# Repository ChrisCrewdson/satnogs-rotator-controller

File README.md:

# SatNOGS Rotator Controller

Firmware and electronics designs for [SatNOGS Rotator](https://github.com/satnogs/satnogs-rotator/).

Repository includes all source files for PCB's and firmware for the SatNOGS rotator controller assembly.

## Documentation

More information can be found in our [documentation](http://satnogs.org/documentation/hardware/), or our [wiki](https://wiki.satnogs.org).

Please check the documentation to find which release of the rotator controller matches your mechanical rotator version.

## Repository policy
SatNOGS hardware repositories only track source design files. All needed derivative files (e.g. stl, grb etc) for production are created per release, packaged in an archive and uploaded linked to a  [release](https://github.com/satnogs/satnogs-rotator-controller/releases).

Each major release (x.0.0) is branched out of master. Subsequent fixes (minor or not) are commited on those branches and tagged accordingly.

Master branch is most times under active development, so expect things to break. For production ready and previous releases source files check tags and branches.

## License

&copy; 2014-2015 [Libre Space Foundation](http://librespacefoundation.org).

Licensed under the [CERN OHLv1.2](LICENSE).

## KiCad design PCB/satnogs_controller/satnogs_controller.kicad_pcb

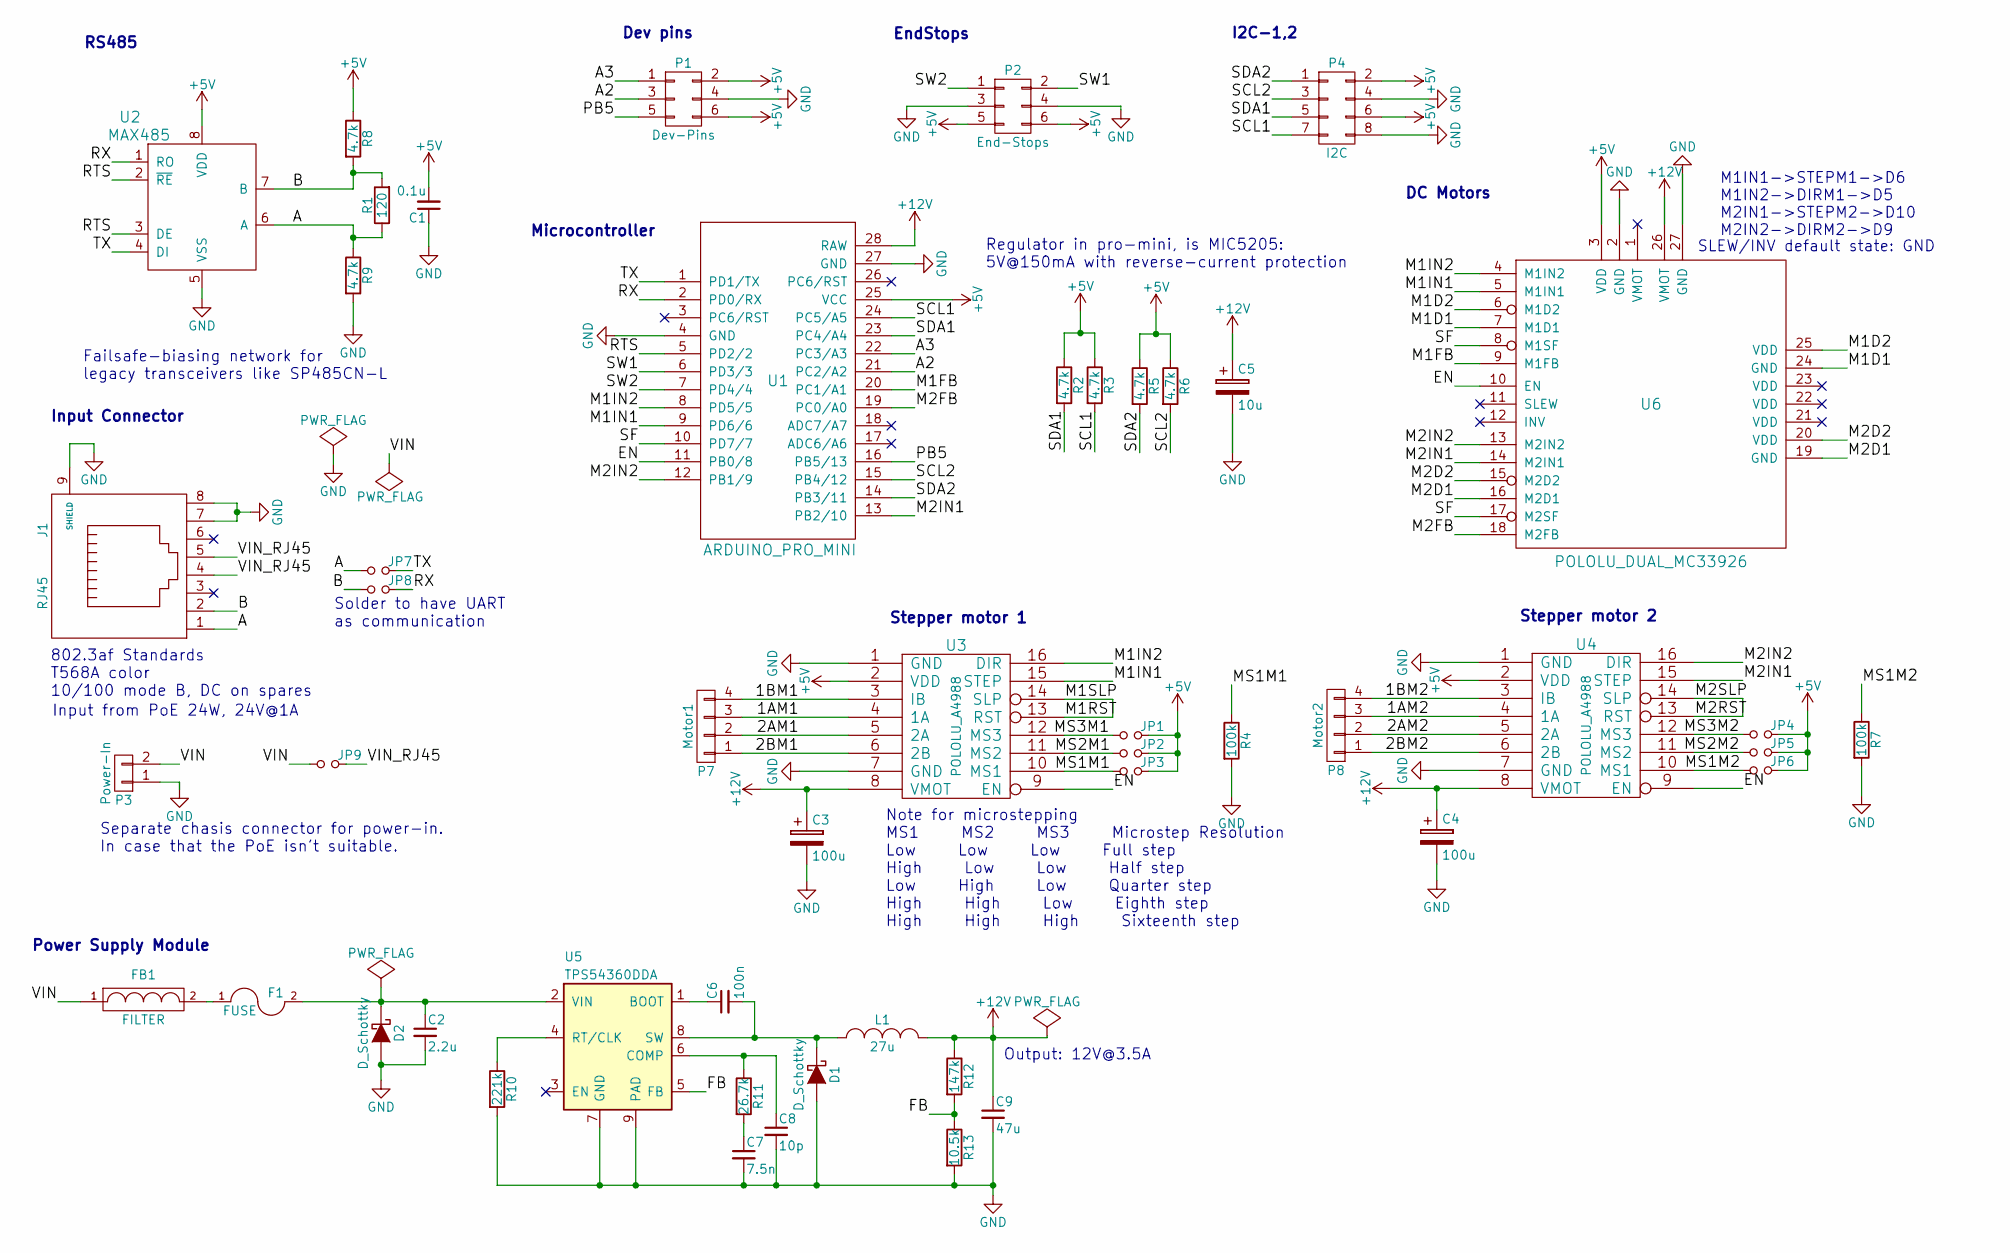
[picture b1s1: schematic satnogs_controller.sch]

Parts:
C1: 0.1u; C_0805_HandSoldering
C2: 2.2u; C_1210
C3, C4: 100u; C_Radial_D6.3_L11.2_P2.5
C5: 10u; C_Radial_D6.3_L11.2_P2.5
C6: 100n; C_0805_HandSoldering
C7: 7.5n; C_0805_HandSoldering
C8: 10p; C_0805_HandSoldering
C9: 47u; C_1210
D1, D2: D_Schottky; DO-214AB
F1: FUSE; Fuse_SMD
FB1: FILTER; R_0805_HandSoldering
J1: RJ45; RJ45_8
JP1, JP2, JP3, JP4, JP5, JP6, JP7, JP8, JP9: Jumper_NO_Small; R_0805_HandSoldering
L1: 27u; bourns-srr1210
P1: Dev-Pins; Pin_Header_Straight_2x03
P2: End-Stops; Pin_Header_Straight_2x03
P3: Power-In; WireConnection_2.00mmDrill
P4: I2C; Pin_Header_Straight_2x04
P7: Motor1; bornier4
P8: Motor2; bornier4
R1: 120; R_0805_HandSoldering
R2, R3, R5, R6, R8, R9: 4.7k; R_0805_HandSoldering
R4, R7: 100k; R_0805_HandSoldering
R10: 221k; R_0805_HandSoldering
R11: 26.7k; R_0805_HandSoldering
R12: 147k; R_0805_HandSoldering
R13: 10.5k; R_0805_HandSoldering
U1: ARDUINO_PRO_MINI; arduino-pro-mini
U2: MAX485; SOIC-8_3.9x4.9mm_Pitch1.27mm
U3, U4: POLOLU_A4988; pololu-a4988
U5: TPS54360DDA; HSOP-8
U6: POLOLU_DUAL_MC33926; pololu-dual-mc33926

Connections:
+5V: C1.2, JP1.2, JP2.2, JP3.2, JP4.2, JP5.2, JP6.2, P1.2, P1.6, P2.5, P2.6, P4.2, P4.6, R2.1, R3.1, R5.1, R6.1, R8.1, U1.25 (VCC), U2.8 (VDD), U3.2 (VDD), U4.2 (VDD), U6.3 (VDD)
+12V: C3.1, C4.1, C5.1, C9.1, L1.2, R12.1, U1.28 (RAW), U3.8 (VMOT), U4.8 (VMOT), U6.26 (VMOT)
/1AM1: P7.3, U3.4 (1A)
/1AM2: P8.3, U4.4 (1A)
/1BM1: P7.4, U3.3 (IB)
/1BM2: P8.4, U4.3 (IB)
/2AM1: P7.2, U3.5 (2A)
/2AM2: P8.2, U4.5 (2A)
/2BM1: P7.1, U3.6 (2B)
/2BM2: P8.1, U4.6 (2B)
/A: J1.1, JP7.1, R1.1, R9.1, U2.6 (A)
/A2: P1.3, U1.21 (PC2/A2)
/A3: P1.1, U1.22 (PC3/A3)
/B: J1.2, JP8.1, R1.2, R8.2, U2.7 (B)
/EN: U1.11 (PB0/8), U3.9 (EN), U4.9 (EN), U6.10 (EN)
/FB: R12.2, R13.1, U5.5 (FB)
/M1D1: U6.7 (M1D1), U6.24 (GND)
/M1D2: U6.6 (M1D2), U6.25 (VDD)
/M1FB: U1.20 (PC1/A1), U6.9 (M1FB)
/M1IN1: U1.9 (PD6/6), U3.15 (STEP), U6.5 (M1IN1)
/M1IN2: U1.8 (PD5/5), U3.16 (DIR), U6.4 (M1IN2)
/M1RST: U3.13 (RST), U3.14 (SLP)
/M2D1: U6.16 (M2D1), U6.19 (GND)
/M2D2: U6.15 (M2D2), U6.20 (VDD)
/M2FB: U1.19 (PC0/A0), U6.18 (M2FB)
/M2IN1: U1.13 (PB2/10), U4.15 (STEP), U6.14 (M2IN1)
/M2IN2: U1.12 (PB1/9), U4.16 (DIR), U6.13 (M2IN2)
/M2RST: U4.13 (RST), U4.14 (SLP)
/MS1M1: JP3.1, R4.1, U3.10 (MS1)
/MS1M2: JP6.1, R7.1, U4.10 (MS1)
/MS2M1: JP2.1, U3.11 (MS2)
/MS2M2: JP5.1, U4.11 (MS2)
/MS3M1: JP1.1, U3.12 (MS3)
/MS3M2: JP4.1, U4.12 (MS3)
/PB5: P1.5, U1.16 (PB5/13)
/RTS: U1.5 (PD2/2), U2.2 (~RE), U2.3 (DE)
/RX: JP8.2, U1.2 (PD0/RX), U2.1 (RO)
/SCL1: P4.7, R3.2, U1.24 (PC5/A5)
/SCL2: P4.3, R6.2, U1.15 (PB4/12)
/SDA1: P4.5, R2.2, U1.23 (PC4/A4)
/SDA2: P4.1, R5.2, U1.14 (PB3/11)
/SF: U1.10 (PD7/7), U6.8 (M1SF), U6.17 (M2SF)
/SW1: P2.2, U1.6 (PD3/3)
/SW2: P2.1, U1.7 (PD4/4)
/TX: JP7.2, U1.1 (PD1/TX), U2.4 (DI)
/VIN: FB1.1, JP9.1, P3.2
/VIN_RJ45: J1.4, J1.5, JP9.2
GND: C1.1, C2.2, C3.2, C4.2, C5.2, C7.2, C8.2, C9.2, D1.2 (A), D2.2 (A), J1.7, J1.8, J1.9 (SHIELD), P1.4, P2.3, P2.4, P3.1, P4.4, P4.8, R4.2, R7.2, R9.2, R10.2, R13.2, U1.4 (GND), U1.27 (GND), U2.5 (VSS), U3.1 (GND), U3.7 (GND), U4.1 (GND), U4.7 (GND), U5.7 (GND), U5.9 (PAD), U6.2 (GND), U6.27 (GND)
unnamed: C2.1, D2.1 (K), F1.2, U5.2 (VIN)
unnamed: C6.1, U5.1 (BOOT)
unnamed: C6.2, D1.1 (K), L1.1, U5.8 (SW)
unnamed: C7.1, R11.2
unnamed: C8.1, R11.1, U5.6 (COMP)
unnamed: F1.1, FB1.2
unnamed: R10.1, U5.4 (RT/CLK)

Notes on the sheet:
M1IN1->STEPM1->D6 M1IN2->DIRM1->D5 M2IN1->STEPM2->D10 M2IN2->DIRM2->D9
I2C-1,2
EndStops
DC Motors
Microcontroller
RS485
Stepper motor 1
Stepper motor 2
Dev pins
Regulator in pro-mini, is MIC5205: 5V@150mA with reverse-current protection
Failsafe-biasing network for legacy transceivers like SP485CN-L
Input Connector
Note for microstepping MS1 MS2 MS3 Microstep Resolution Low Low Low Full step High Low Low Half step Low High Low Quarter step High High Low Eighth step High High High Sixteenth step
802.3af Standards T568A color 10/100 mode B, DC on spares
Input from PoE 24W, 24V@1A
SLEW/INV default state: GND
Power Supply Module
Solder to have UART as communication
Output: 12V@3.5A
Separate chasis connector for power-in. In case that the PoE isn't suitable.

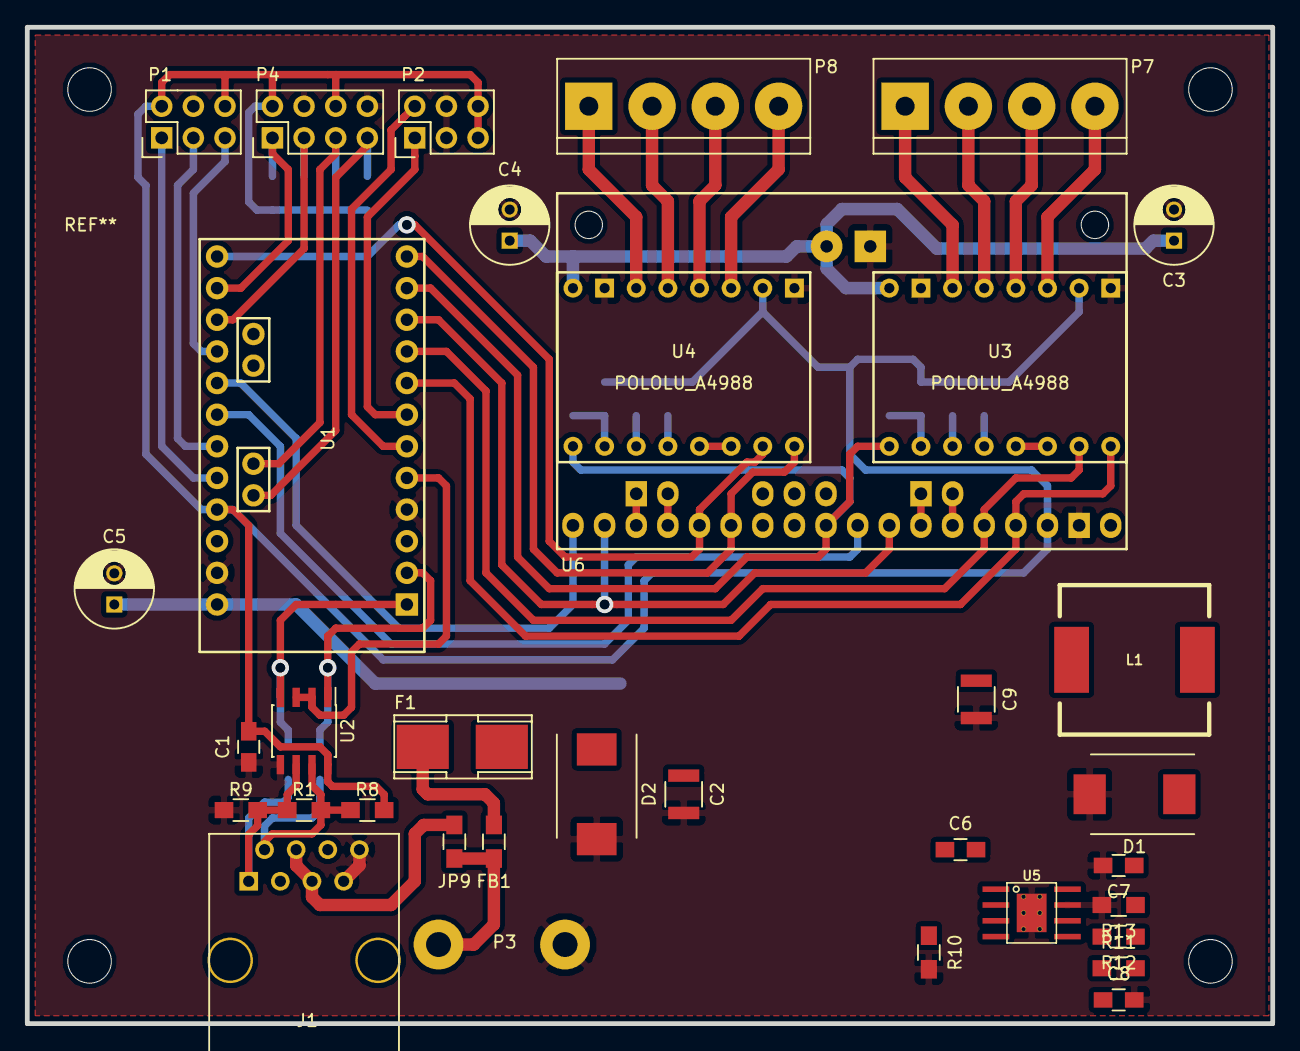
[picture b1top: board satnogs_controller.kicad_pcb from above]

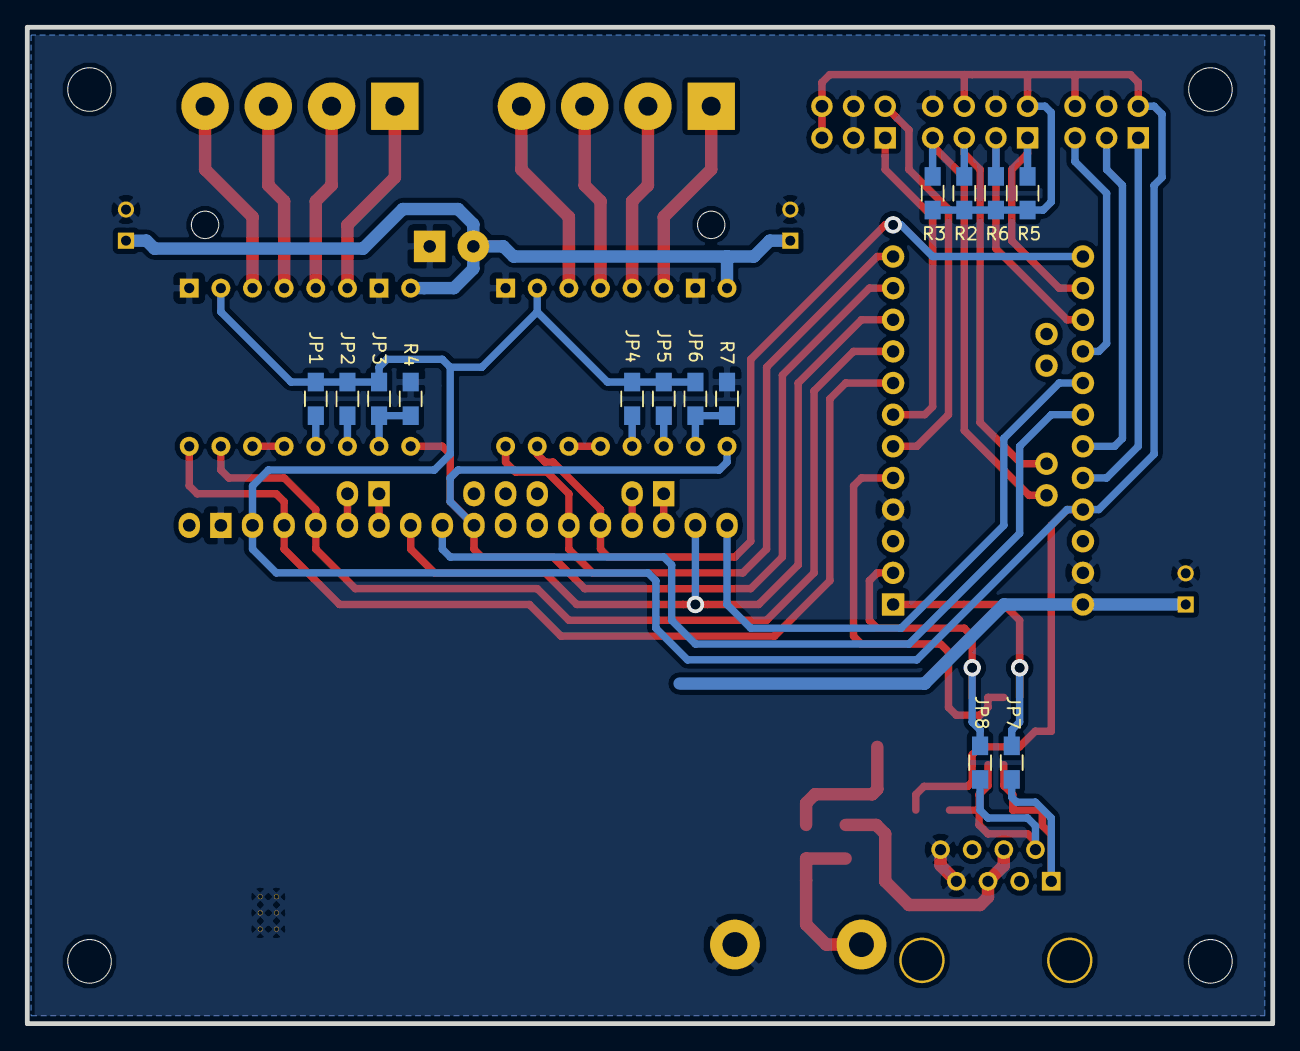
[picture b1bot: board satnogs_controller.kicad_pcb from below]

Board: 2 copper layers, 100.0 x 80.0 mm, 49 parts (14 on the bottom side), 55 nets.

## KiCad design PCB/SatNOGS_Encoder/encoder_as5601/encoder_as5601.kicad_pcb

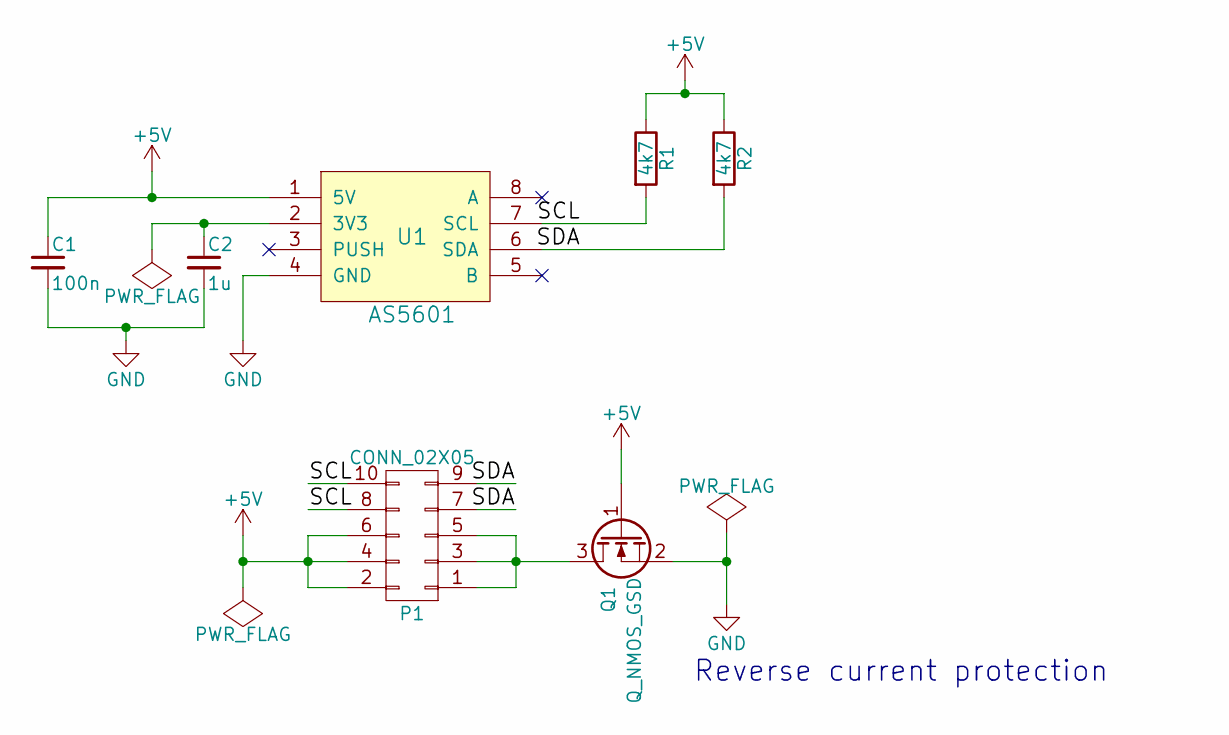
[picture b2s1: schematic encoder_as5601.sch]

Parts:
C1: 100n; C_0805_HandSoldering
C2: 1u; C_0805_HandSoldering
P1: CONN_02X05; Pin_Header_Straight_2x05
Q1: Q_NMOS_GSD; SOT-23_Handsoldering
R1, R2: 4k7; R_0805_HandSoldering
U1: AS5601; SOIC-8_3.9x4.9mm_Pitch1.27mm

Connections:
+5V: C1.1, P1.2, P1.4, P1.6, Q1.1 (G), R1.1, R2.1, U1.1 (5V)
/SCL: P1.8, P1.10, R1.2, U1.7 (SCL)
/SDA: P1.7, P1.9, R2.2, U1.6 (SDA)
GND: C1.2, C2.2, Q1.2 (S), U1.4 (GND)
unnamed: C2.1, U1.2 (3V3)
unnamed: P1.1, P1.3, P1.5, Q1.3 (D)

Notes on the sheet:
Reverse current protection

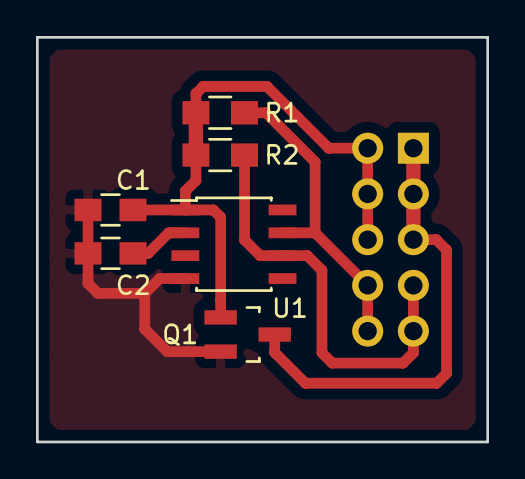
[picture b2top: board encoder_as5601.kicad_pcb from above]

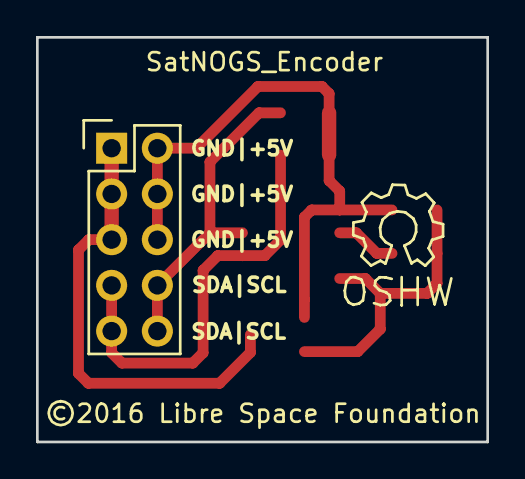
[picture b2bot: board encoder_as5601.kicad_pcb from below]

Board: 2 copper layers, 25.0 x 22.5 mm, 8 parts (2 on the bottom side), 6 nets.

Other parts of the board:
SatNOGS_Encoder: ©2016 Libre Space Foundation; Symbol_OSHW-Logo_SilkScreen

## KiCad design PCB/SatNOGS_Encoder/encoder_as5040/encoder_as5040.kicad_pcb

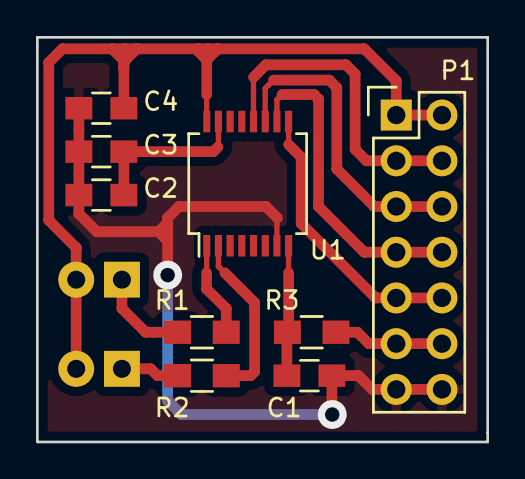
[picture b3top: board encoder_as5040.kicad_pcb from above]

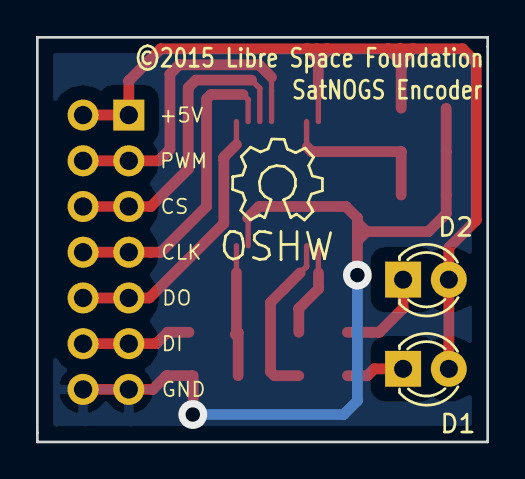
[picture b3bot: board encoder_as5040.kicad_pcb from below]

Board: 2 copper layers, 25.0 x 22.5 mm, 12 parts (3 on the bottom side), 13 nets.

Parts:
C1: 1n; C_0805_HandSoldering
C2, C3: 1u; C_0805_HandSoldering
C4: 100n; C_0805_HandSoldering
D1, D2: LED; LED-3MM
P1: CONN_02X07; Pin_Header_Straight_2x07
R1, R2: 560; R_0805_HandSoldering
R3: 100; R_0805_HandSoldering
U1: AS5040; SSOP-16_5.3x6.2mm_Pitch0.65mm
©2015 Libre Space Foundation: SatNOGS Encoder; Symbol_OSHW-Logo_SilkScreen

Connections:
+5V: C4.1, D1.2, D2.2, P1.1, P1.2, U1.16
/CLK: P1.7, P1.8, U1.10
/CS: P1.5, P1.6, U1.11
/DI: P1.11, P1.12, R3.1
/DO: P1.9, P1.10, U1.9
/MagDECn: R2.2, U1.2
/MagINCn: R1.2, U1.1
/PWM: P1.3, P1.4, U1.12
/Prog: C1.2, R3.2, U1.8
GND: C1.1, C2.2, C3.2, C4.2, P1.13, P1.14, U1.7
unnamed: C2.1, C3.1, U1.15
unnamed: D1.1, R1.1
unnamed: D2.1, R2.1

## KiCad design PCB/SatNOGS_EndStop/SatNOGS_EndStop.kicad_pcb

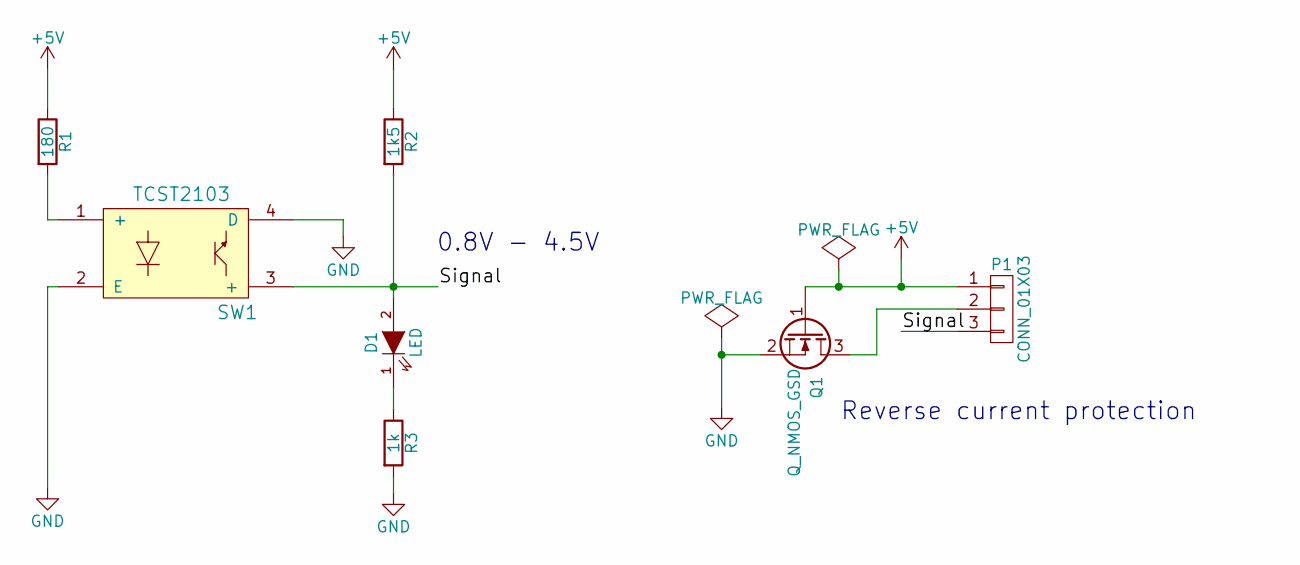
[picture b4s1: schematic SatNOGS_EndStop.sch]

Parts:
D1: LED; LED-3MM
P1: CONN_01X03; Pin_Header_Angled_1x03
Q1: Q_NMOS_GSD; SOT-23_Handsoldering
R1: 180; R_0805_HandSoldering
R2: 1k5; R_0805_HandSoldering
R3: 1k; R_0805_HandSoldering
SW1: TCST2103

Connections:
+5V: P1.1, Q1.1 (G), R1.1, R2.1
/Signal: D1.2 (A), P1.3, R2.2, SW1.3 (+)
GND: Q1.2 (S), R3.2, SW1.2 (E), SW1.4 (D)
unnamed: D1.1 (K), R3.1
unnamed: P1.2, Q1.3 (D)
unnamed: R1.2, SW1.1 (+)

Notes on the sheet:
Reverse current protection
0.8V - 4.5V

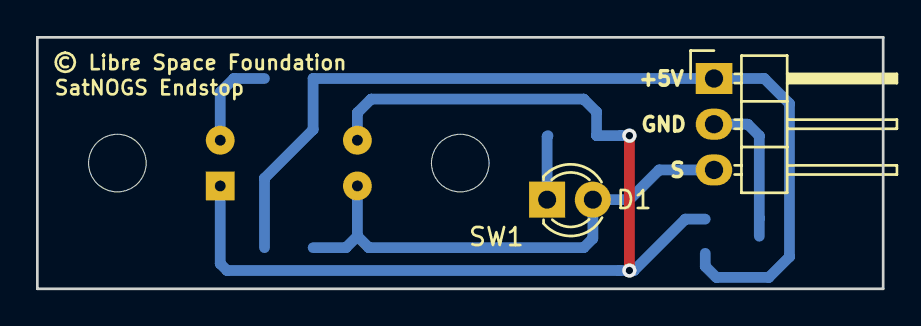
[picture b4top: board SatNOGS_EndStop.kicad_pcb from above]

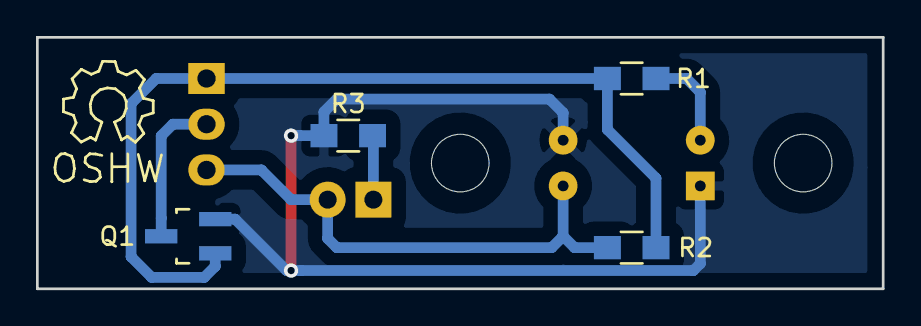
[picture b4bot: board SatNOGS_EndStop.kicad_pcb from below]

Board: 2 copper layers, 47.0 x 14.0 mm, 8 parts (5 on the bottom side), 6 nets.

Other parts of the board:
SatNOGS Endstop: © Libre Space Foundation; Symbol_OSHW-Logo_SilkScreen

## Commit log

2016-11-22 minor bits
